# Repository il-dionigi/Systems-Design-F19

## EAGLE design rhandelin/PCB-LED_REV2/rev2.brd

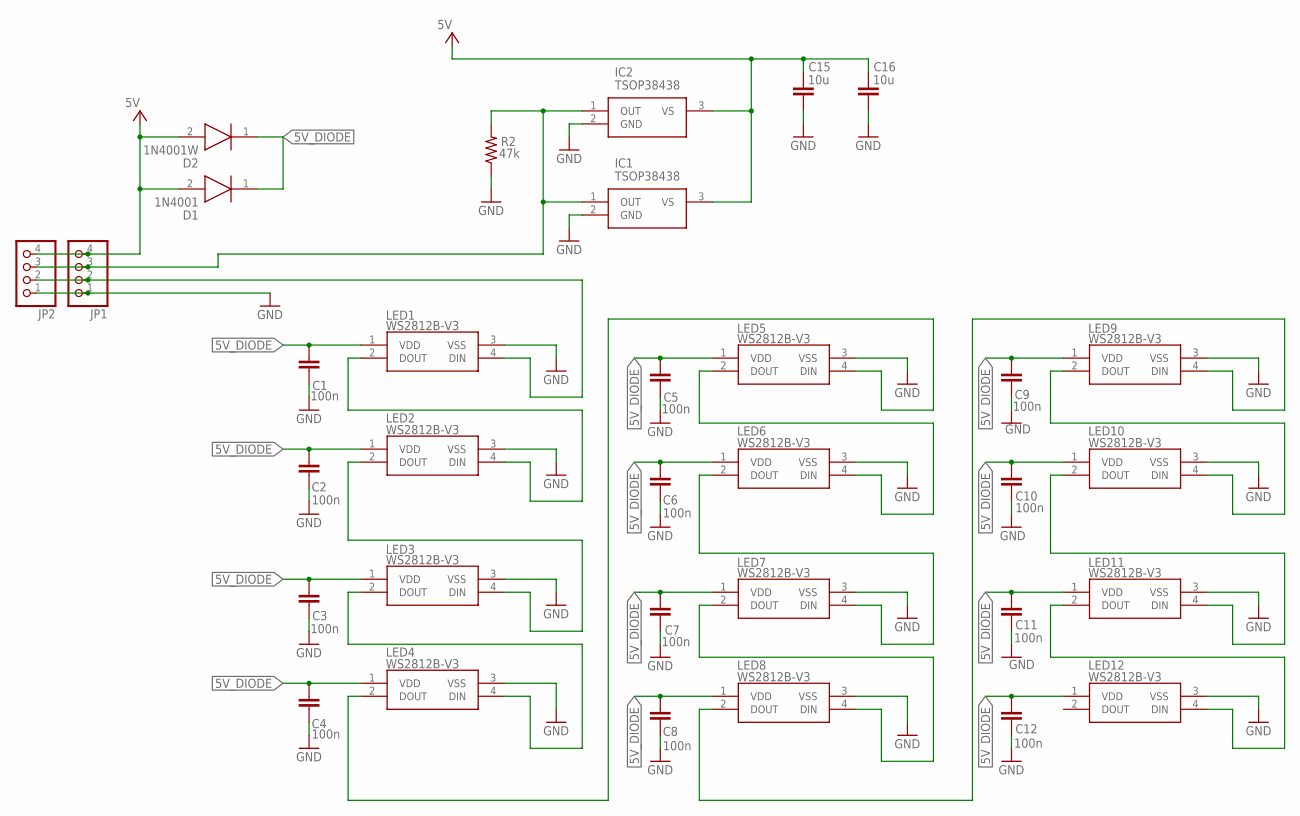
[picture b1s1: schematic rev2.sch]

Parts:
C1, C2, C3, C4, C5, C6, C7, C8, C9, C10, C11, C12: 100n; C0805
C15, C16: 10u; C0805
D1: 1N4001; DIOAD1405W86L465D235
D2: 1N4001W
IC1, IC2: TSOP38438; TSOP38238
JP1, JP2: PINHD-1X4; 1X04
LED1, LED2, LED3, LED4, LED5, LED6, LED7, LED8, LED9, LED10, LED11, LED12: WS2812B-V3; WS2812BV3
R2: 47k; R0805

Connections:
5V: C15.2, C16.2, D1.2 (A), D2.2 (A), IC1.3 (VS), IC2.3 (VS), JP1.4, JP2.4
5V_DIODE: C1.2, C2.1, C3.2, C4.1, C5.2, C6.1, C7.2, C8.1, C9.2, C10.1, C11.2, C12.1, D1.1 (K), D2.1 (K), LED1.1 (VDD), LED2.1 (VDD), LED3.1 (VDD), LED4.1 (VDD), LED5.1 (VDD), LED6.1 (VDD), LED7.1 (VDD), LED8.1 (VDD), LED9.1 (VDD), LED10.1 (VDD), LED11.1 (VDD), LED12.1 (VDD)
GND: C1.1, C2.2, C3.1, C4.2, C5.1, C6.2, C7.1, C8.2, C9.1, C10.2, C11.1, C12.2, C15.1, C16.1, IC1.2 (GND), IC2.2 (GND), JP1.1, JP2.1, LED1.3 (VSS), LED2.3 (VSS), LED3.3 (VSS), LED4.3 (VSS), LED5.3 (VSS), LED6.3 (VSS), LED7.3 (VSS), LED8.3 (VSS), LED9.3 (VSS), LED10.3 (VSS), LED11.3 (VSS), LED12.3 (VSS), R2.1
unnamed: LED1.2 (DOUT), LED2.4 (DIN)
unnamed: IC1.1 (OUT), IC2.1 (OUT), JP1.3, JP2.3, R2.2
unnamed: JP1.2, JP2.2, LED1.4 (DIN)
unnamed: LED3.2 (DOUT), LED4.4 (DIN)
unnamed: LED2.2 (DOUT), LED3.4 (DIN)
unnamed: LED5.2 (DOUT), LED6.4 (DIN)
unnamed: LED4.2 (DOUT), LED5.4 (DIN)
unnamed: LED7.2 (DOUT), LED8.4 (DIN)
unnamed: LED6.2 (DOUT), LED7.4 (DIN)
unnamed: LED9.2 (DOUT), LED10.4 (DIN)
unnamed: LED8.2 (DOUT), LED9.4 (DIN)
unnamed: LED11.2 (DOUT), LED12.4 (DIN)
unnamed: LED10.2 (DOUT), LED11.4 (DIN)

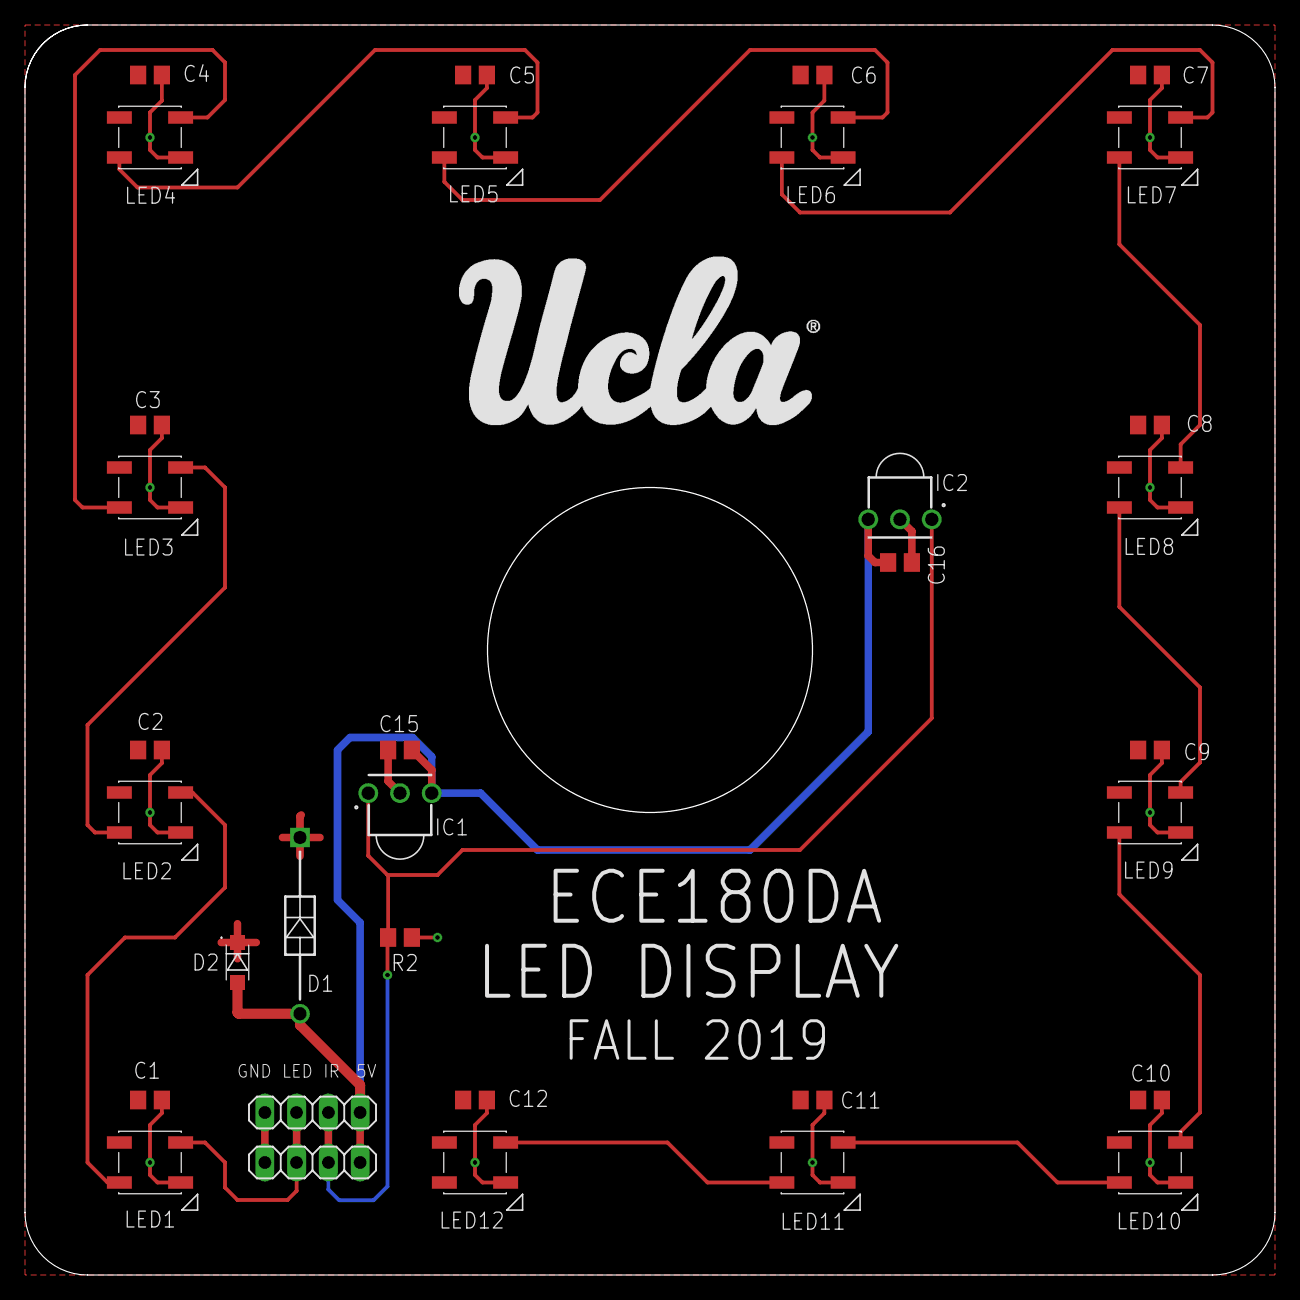
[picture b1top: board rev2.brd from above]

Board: 2 copper layers, 99.9 x 99.9 mm, 33 parts (0 on the bottom side), 16 nets.

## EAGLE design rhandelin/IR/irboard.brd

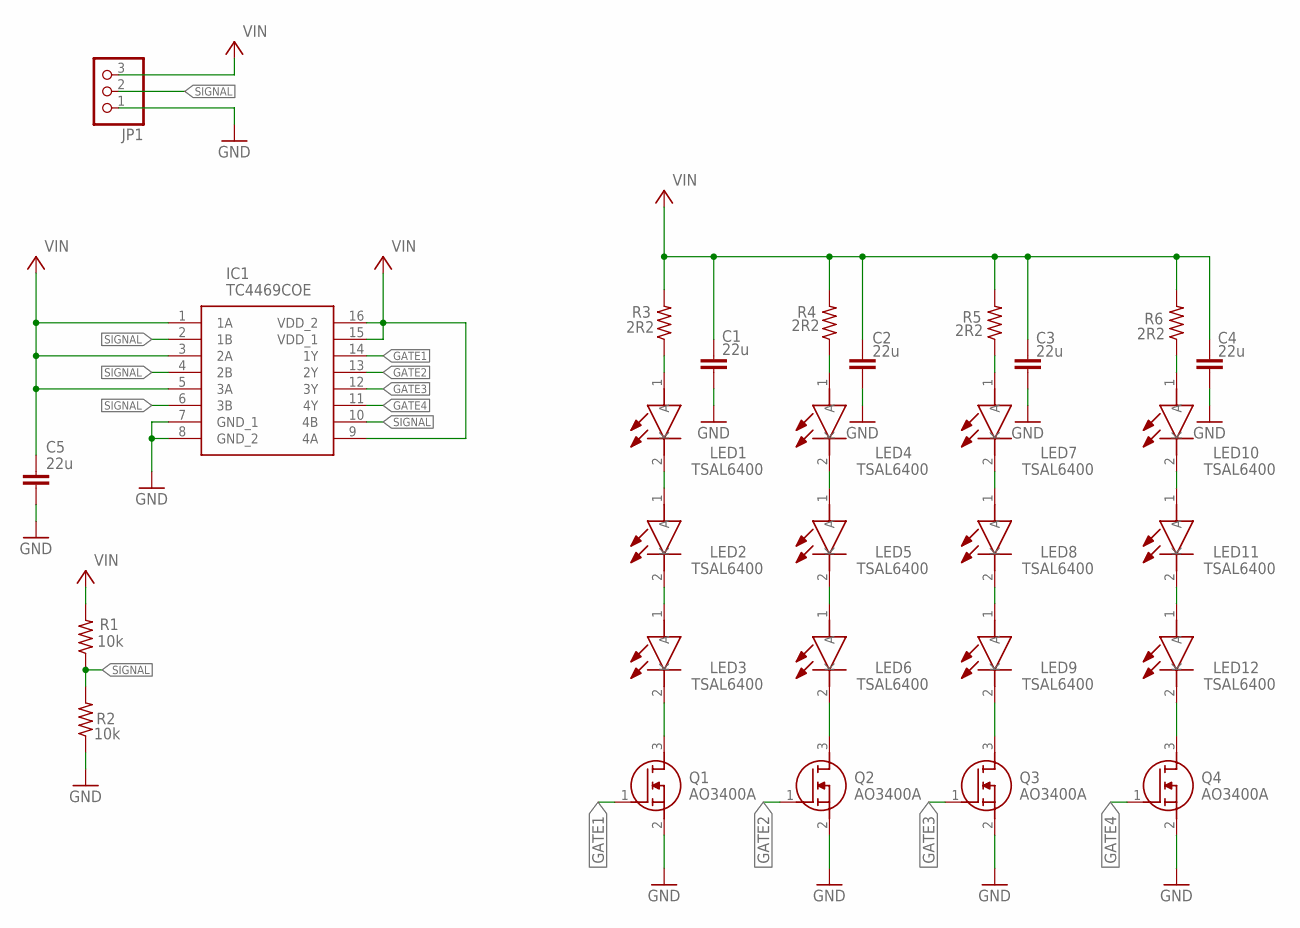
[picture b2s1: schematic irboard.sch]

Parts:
C1, C2, C3, C4, C5: 22u; C0805
IC1: TC4469COE; SOIC127P1034X264-16N
JP1: PINHD-1X3; 1X03
LED1, LED2, LED3, LED4, LED5, LED6, LED7, LED8, LED9, LED10, LED11, LED12: TSAL6400; TSAL6100
Q1, Q2, Q3, Q4: AO3400A; SOT95P280X125-3N
R1, R2: 10k; R0603
R3, R4, R5, R6: 2R2; R0603

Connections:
GATE1: IC1.14 (1Y), Q1.1 (G)
GATE2: IC1.13 (2Y), Q2.1 (G)
GATE3: IC1.12 (3Y), Q3.1 (G)
GATE4: IC1.11 (4Y), Q4.1 (G)
GND: C1.2, C2.2, C3.2, C4.2, C5.2, IC1.7 (GND_1), IC1.8 (GND_2), JP1.1, Q1.2 (S), Q2.2 (S), Q3.2 (S), Q4.2 (S), R2.1
unnamed: LED3.2 (K), Q1.3 (D)
unnamed: LED2.2 (K), LED3.1 (A)
unnamed: LED1.2 (K), LED2.1 (A)
unnamed: LED4.2 (K), LED5.1 (A)
unnamed: LED5.2 (K), LED6.1 (A)
unnamed: LED6.2 (K), Q2.3 (D)
unnamed: LED7.2 (K), LED8.1 (A)
unnamed: LED8.2 (K), LED9.1 (A)
unnamed: LED9.2 (K), Q3.3 (D)
unnamed: LED10.2 (K), LED11.1 (A)
unnamed: LED11.2 (K), LED12.1 (A)
unnamed: LED12.2 (K), Q4.3 (D)
unnamed: LED1.1 (A), R3.1
unnamed: LED4.1 (A), R4.1
unnamed: LED7.1 (A), R5.1
unnamed: LED10.1 (A), R6.1
SIGNAL: IC1.2 (1B), IC1.4 (2B), IC1.6 (3B), IC1.10 (4B), JP1.2, R1.1, R2.2
VIN: C1.1, C2.1, C3.1, C4.1, C5.1, IC1.1 (1A), IC1.3 (2A), IC1.5 (3A), IC1.9 (4A), IC1.15 (VDD_1), IC1.16 (VDD_2), JP1.3, R1.2, R3.2, R4.2, R5.2, R6.2

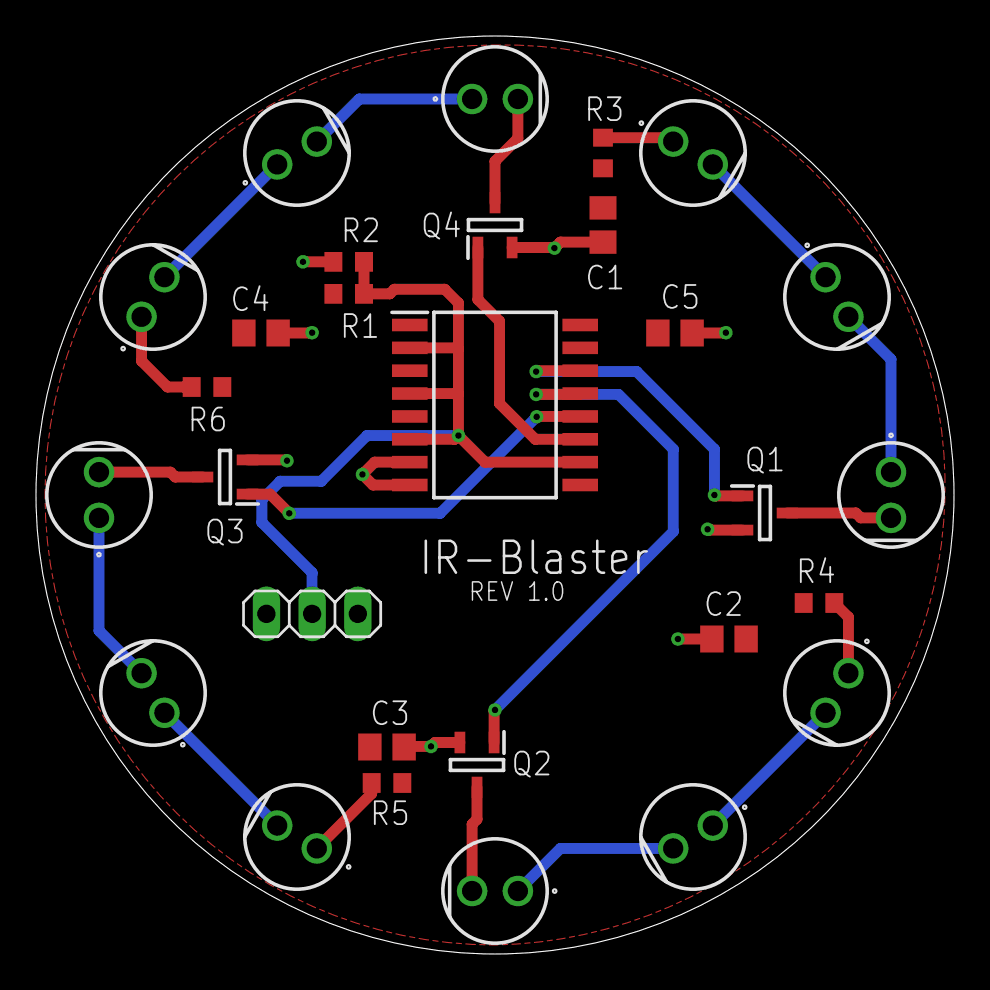
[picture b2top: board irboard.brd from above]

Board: 2 copper layers, 51.0 x 51.0 mm, 29 parts (0 on the bottom side), 23 nets.

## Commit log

2019-09-27 Task 2
    File with my name as it's name
2019-09-27 Task 4
    Branch with my contact info
2019-09-27 Create test.txt
    hi
2019-09-27 Create charleszaloom.txt
    Test
2019-09-27 Create richardhandelin.txt
    Testing
2019-09-27 Added contact info
2019-09-27 Create <sadaf>
2019-09-27 Test
2019-09-27 Whoops
    whoopsie
2019-10-03 Adding FPS.py
    Showcases 2 methods for improving frames per second during runtime.
2019-10-04 Red Blob Tracker
    Tracks red blobs
2019-10-11 message
2019-10-11 Created folder
2019-10-11 Part 3
2019-10-11 Added test.py
2019-10-11 Add serverTest.py
2019-10-11 add clientTest.py
2019-10-11 Digit identifier
2019-10-11 update client
2019-10-11 update server
2019-10-11 Client + Server Files
2019-10-11 server test
2019-10-11 newstuff
2019-10-11 changed port
2019-10-11 changed ip address
2019-10-11 camera stuff
2019-10-11 More camera
2019-10-11 new camear
2019-10-12 python test image
2019-10-12 Camera stuff
    capture script + image
2019-10-12 more things
2019-10-18 QR2
    Requires Zbar
2019-11-07 Python Google Sheets
    preliminary algorithm for seat order
2019-11-07 PCB Files
2019-11-07 Add Eagle Files
2019-11-07 Add oscilloscope capture
2019-11-08 Added controlpi software dataframe
2019-11-08 adding BLE
2019-11-08 BLE update
2019-11-08 Adding Broadcast Template
2019-11-09 Update BLE
2019-11-11 Web Interface Added
2019-11-14 New Schematic/PCB
2019-11-15 Add python test scripts
2019-11-15 BLE Stuff
2019-11-15 BLE pt 2
2019-11-15 BLE fix
2019-11-15 TABS
2019-11-21 Report / Updated CSS
2019-11-21 BLE Listen Update
2019-11-21 Created BLE.py
2019-11-21 Update BLE.py
    Final Configuration.
    Three Defined User Functions
2019-11-22 Cleaned BLE
2019-11-22 Restructure
2019-11-22 Update pcb
2019-11-22 ewfewas
2019-11-22 please
2019-11-22 maybe
2019-11-22 udate
2019-11-22 last one
2019-11-22 one more time
2019-11-22 adsfgh
2019-11-22 Add Gerber
2019-11-22 flags
2019-11-22 this obe
2019-11-22 afdsgdhetgrtwagsrshtewrgs
2019-11-22 help
2019-11-23 udpate
2019-11-23 Gui Update
2019-12-05 BLE Messages are sent through my controlpy script
2019-12-05 Mk1 Project Folder
2019-12-05 Created Example.py
2019-12-05 Added input redundancy
2019-12-05 mapping and encoding
    added some of my files with (hopefully) helpful comments
2019-12-06 Added my interface
2019-12-06 Setup PixelPi
2019-12-06 stuff
2019-12-06 My python solution
2019-12-06 Pixel
2019-12-06 Blah
2019-12-06 update pixel
2019-12-06 ledtest
2019-12-06 update ledtest
2019-12-06 qwefg
2019-12-06 pillow requirements
2019-12-06 Synthesized pixelAndrew
2019-12-06 encode update
2019-12-07 Integration updates
2019-12-07 indents
2019-12-07 Udpate pixel
2019-12-07 strdytfygkhujl
2019-12-07 wsef
2019-12-07 fixed?
2019-12-07 updated encoder
    Encoder now accepts list of arrays/tuples with the format for each being [id, x, y]
2019-12-07 ewrgh
2019-12-07 qdwf
2019-12-07 Andrew Changes
2019-12-07 Encoder
2019-12-07 MVP
    Project works with defined, unwatned behavior
2019-12-07 Added reset
    Added reset to routine 0 and tested it works
2019-12-07 Got website working on rbpi
2019-12-10 finite routine
    routine flag is now reset
2019-12-10 routine in interrupt
    Routine now runs from the routine
2019-12-10 sdfsdf
2019-12-10 deleted settings
    muahahaha
2020-01-30 remove berryconda
2020-01-30 Made Richard's Code a Class, Added More Patterns, Started Implementing Localization
